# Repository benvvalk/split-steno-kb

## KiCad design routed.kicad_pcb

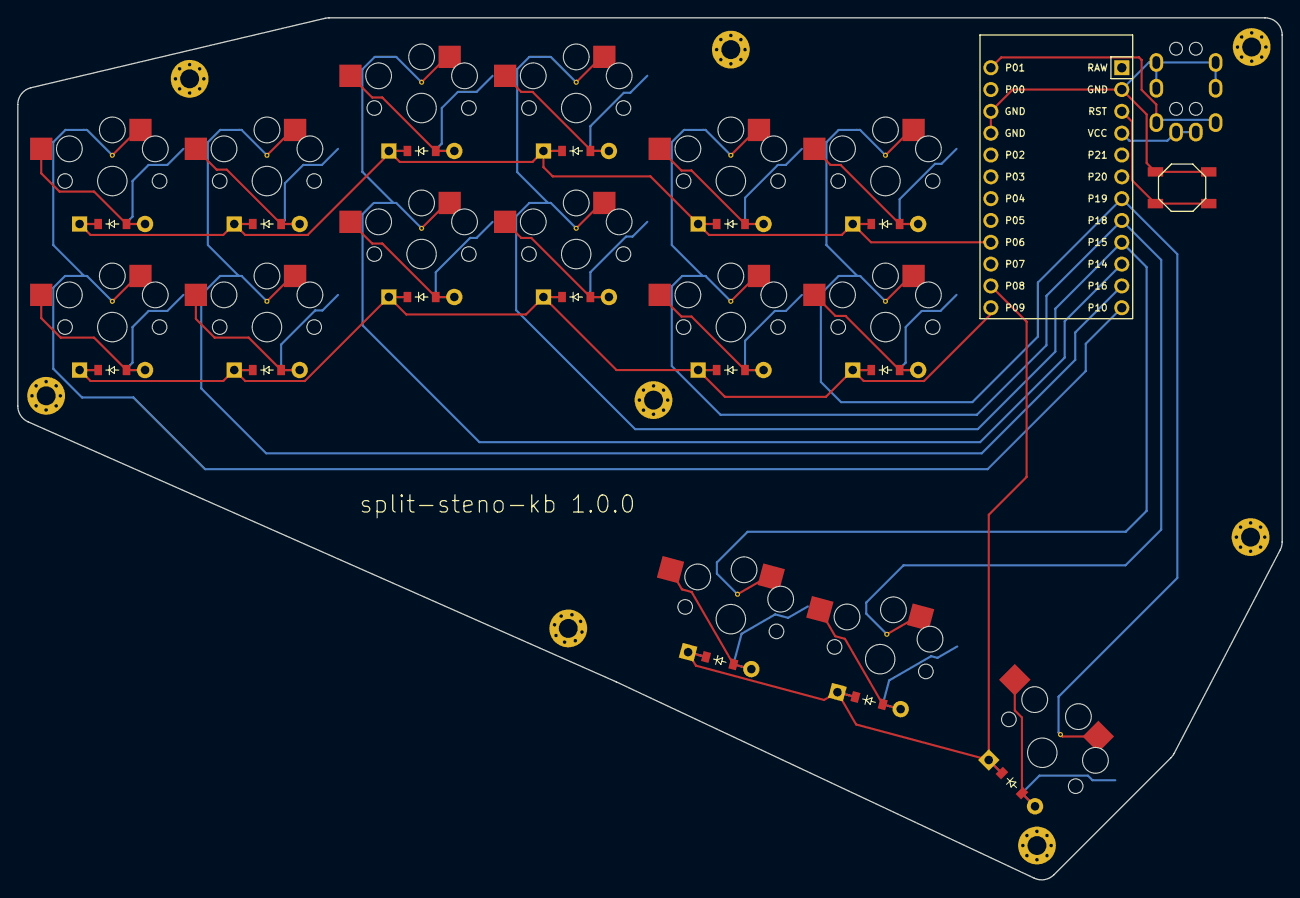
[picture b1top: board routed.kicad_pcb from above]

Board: 2 copper layers, 147.2 x 100.3 mm, 41 parts (0 on the bottom side), 28 nets.

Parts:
B1: SW_TACT_ALPS_SKQGABE010
D1, D2, D3, D4, D5, D6, D7, D8, D9, D10, D11, D12, D13, D14, D15: ComboDiode
MCU1: ProMicro
S1, S2, S3, S4, S5, S6, S7, S8, S9, S10, S11, S12, S13, S14, S15: PG1350
TRRS1: TRRS-PJ-320A-dual
_16, _17, _18, _19, _20, _21, _22, _23: MountingHole_2.2mm_M2_Pad_Via

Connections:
GND: B1.1, MCU1.2, MCU1.15, MCU1.16, TRRS1.3, TRRS1.4
P1: MCU1.13, TRRS1.2
P6: D2.1, D4.1, D6.1, D8.1, D10.1, D12.1, MCU1.21
P8: D13.1, D14.1, D15.1, MCU1.23
P9: D1.1, D3.1, D5.1, D7.1, D9.1, D11.1, MCU1.24
P10: MCU1.12, S1.1, S2.1
P14: MCU1.10, S5.1, S6.1
P15: MCU1.9, S7.1, S8.1, S13.1
P16: MCU1.11, S3.1, S4.1
P18: MCU1.8, S9.1, S10.1, S14.1
P19: MCU1.7, S11.1, S12.1, S15.1
RST: B1.2, MCU1.3
VCC: MCU1.4, TRRS1.1
index_bottom: D9.2, S9.2
index_top: D10.2, S10.2
inner_bottom: D11.2, S11.2
inner_row0: D15.2, S15.2
inner_top: D12.2, S12.2
left_row0: D13.2, S13.2
middle_bottom: D7.2, S7.2
middle_top: D8.2, S8.2
outer_bottom: D1.2, S1.2
outer_top: D2.2, S2.2
pinky_bottom: D3.2, S3.2
pinky_top: D4.2, S4.2
right_row0: D14.2, S14.2
ring_bottom: D5.2, S5.2
ring_top: D6.2, S6.2

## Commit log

2024-07-08 import: ergogen.yaml (initial design) [import]
    Initial design, with only the left half.
2024-07-08 ergogen.yaml: add outlines ("pcb", "keys", "debug") [feat]
2024-07-27 ergogen.yaml: add pcb definition, add promicro and trrs components [feat]
2024-07-27 ergogen.yaml: add reset button [feat]
2024-07-28 import: footprints/mountinghole.js from MvEerd/ergogen bca205f [import]
    Import the M2 mounting hole footprint from the `MvEeerd/ergogen`
    GitHub repo, from commit bca205f.
    I will need M2 mounting holes because, for the keyboard "case", I'm
    planning to vertically stack two identical PCBs joined by M2
    standoffs. The bottom PCB will have no components soldered onto it,
    and its only purpose will be to provide a flat surface for the
2024-08-03 config.yaml: nudge microcontroller position [tweak]
2024-08-03 config.yaml: add mounting holes [feat]
2024-08-04 config.yaml: configure trrs nets [routing]
2024-08-04 config.yaml: configure row and column nets [routing]
2024-08-04 config.yaml: add vias to connect hotswap pads [feat]
    Add per-key vias to connect choc hotswap SMD pads on opposite sides of
    the board.
    This is a reversible PCB, and using vias saves me the additional
    work/complexity of routing the matrix columns on both sides of the
    board.
2024-08-04 import: routed.kicad_* (manually routed PCB) [import]
    Commit the .kicad_pcb and related files after manually adding the
    copper traces to the PCB in KiCad (i.e. the "routing" step).
    Note 1: Ergogen does not perform the routing step because it's too
    hard to automate. Therefore I had to do the routing manually in
    KiCad. That also means that if I ever make further changes to
    `ergogen.yaml` and regenerate, I will need to redo the routing!
2024-08-04 routed.kicad_pcb: fix trrs connections, unconnected diodes [bugfix]
    Connected serial data pin P1 of Arduino to pin 2 of TRRS jack, rather
    than pin 3 of TRRS jack. Using pin 2 for the serial data will allow
    the use of both TRS and TRRS cables, whereas the former use of pin 3
    would only work with TRRS cables.
    Connect some diode pads that I forgot to connect (thanks, Design Rules
    Checker).
2024-08-04 board setup: set "solder mask clearance" to 0 [config]
    In the File -> Board Setup dialog, change "solder mask clearance" from
    0.05 -> 0.
    I'm doing this because there was a warning in the File -> Fabrication
    Outputs -> Gerbers dialog that told me I should do that.
2024-08-04 pcb: add "split-steno-kb 1.0.0" to silkscreen layer [feat]
    Add a version number to the PCB, so I won't get confused if I end up
    making multiple versions of the board.
2024-08-10 import: gerbers.zip [import]
    I generated gerber and drill files from `routed.pcb` using File ->
    Production Outputs -> Gerbers (.gbr)... in KiCad, then zipped them up
    into gerbers.zip.
